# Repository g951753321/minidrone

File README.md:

# Minidrone project

This project is a complex project that involves the firmware development, the schematic, and PCB design for a mini drone.

## Firmware development

The firmware development is done using the Zephyr RTOS. The firmware includes the control algorithms for the drone, and the communication with the MicroBlue application.

### Setup Zephyr RTOS

To setup the Zephyr RTOS, follow the instructions in the [Zephyr RTOS documentation](https://docs.zephyrproject.org/latest/getting_started/index.html).

### Project Initialization

To initial the project, clone the repository and run the following commands:

```bash
west init -m https://github.com/g951753321/minidrone.git --mr main minidrone
cd minidrone
west update
```

### Build the project

To build the project, run the following commands:

```bash
west build -b stm32_dev_min minidrone/apps/PID_control
```

The firmware is built for the `stm32_dev_min` board, and the application is `PID_control`.
The output files are located in the `build/zephyr` directory.

## Schematic and PCB design

The schematic/PCB design is done using KiCad. The schematic includes the design of the motor drivers, the microcontroller, and the sensors.

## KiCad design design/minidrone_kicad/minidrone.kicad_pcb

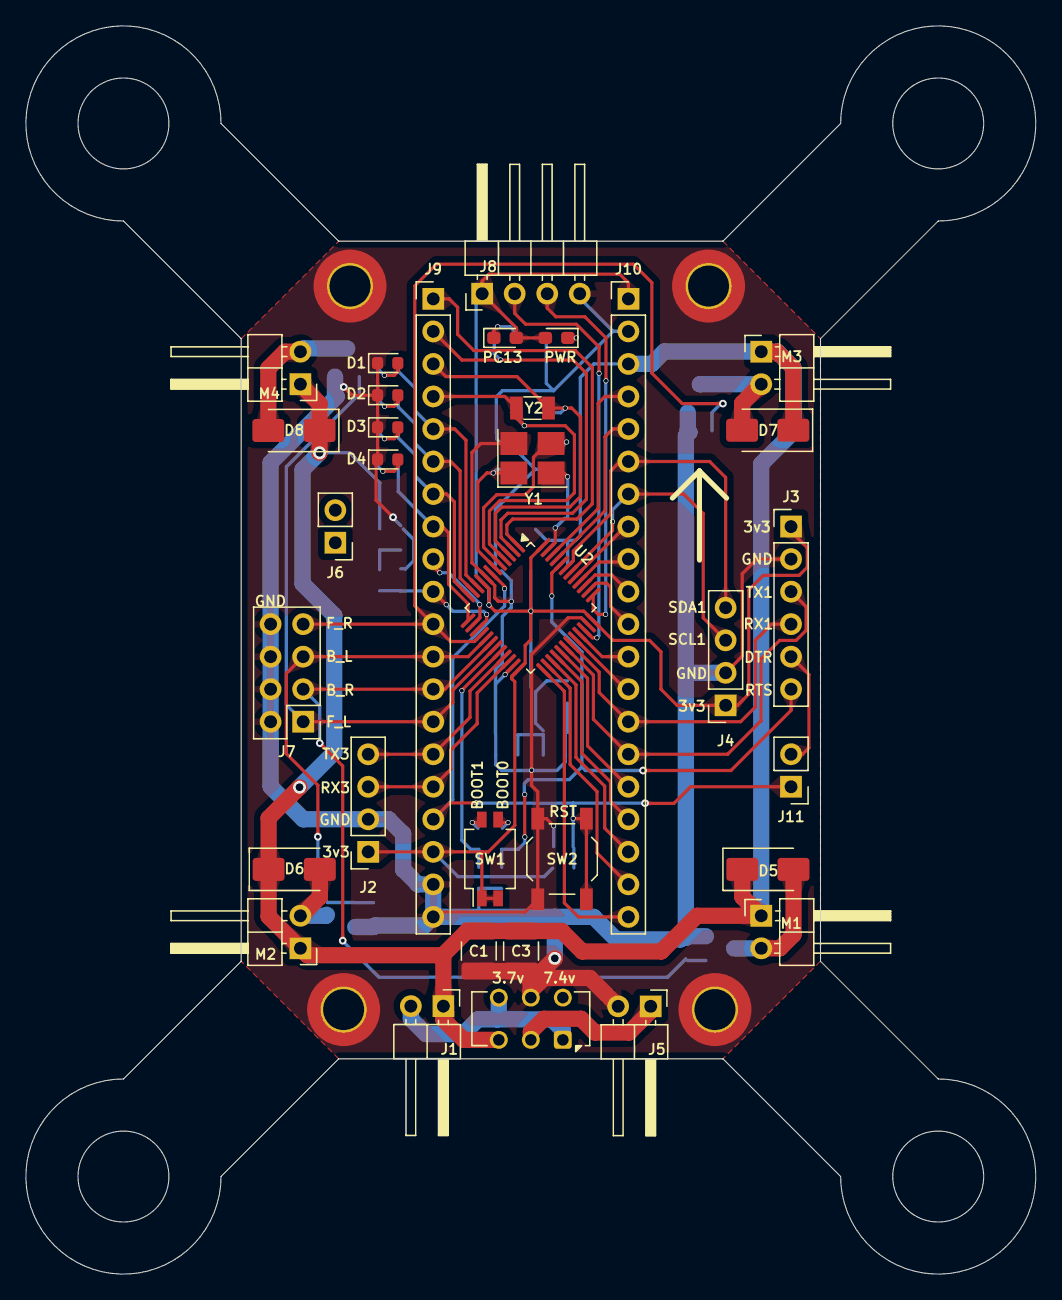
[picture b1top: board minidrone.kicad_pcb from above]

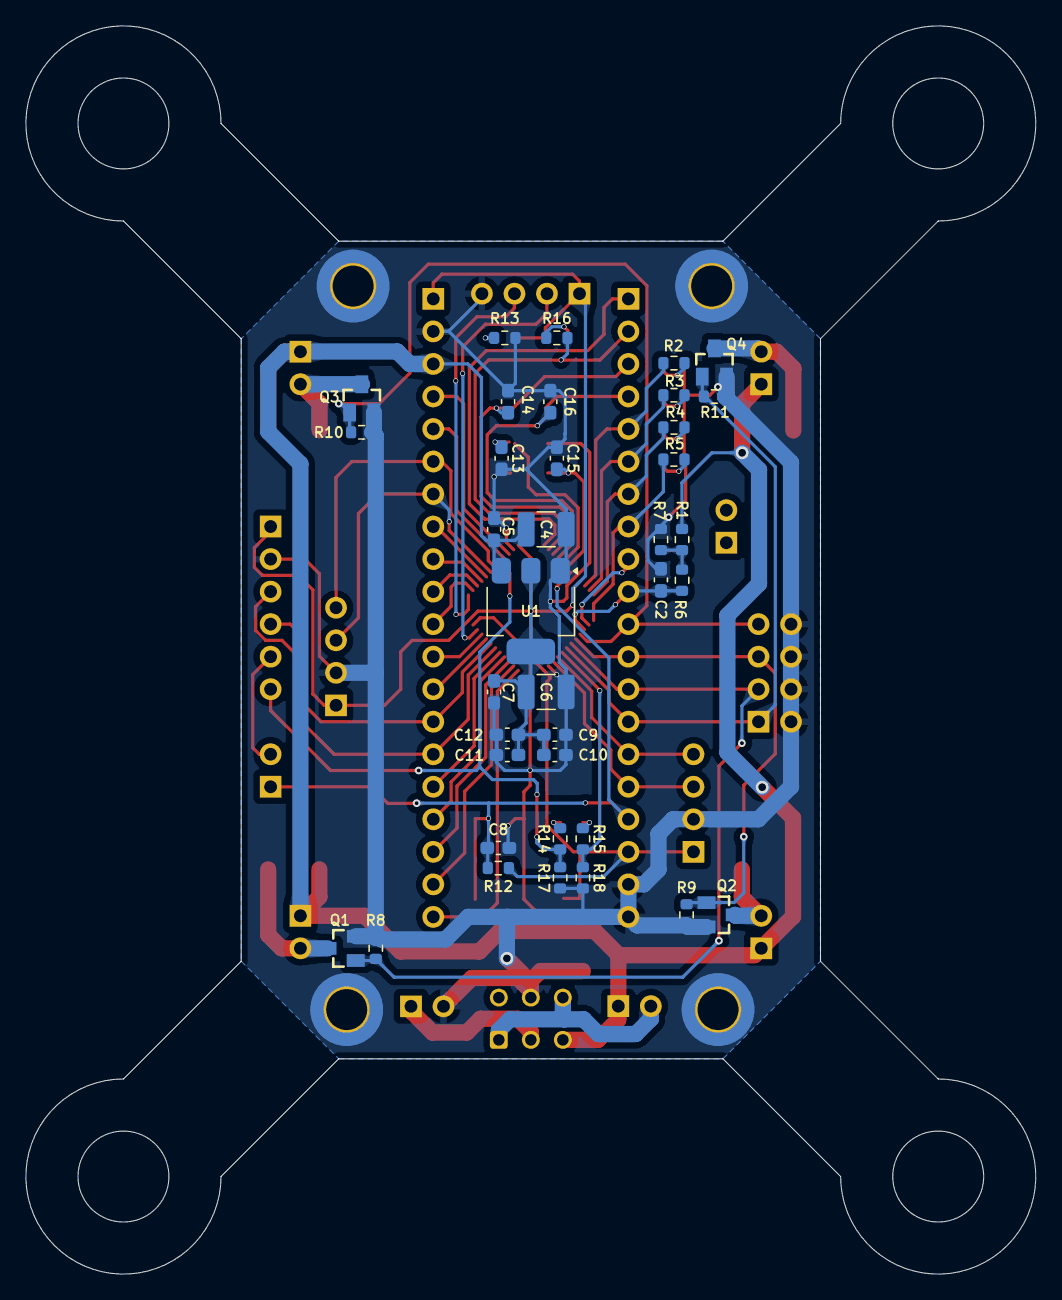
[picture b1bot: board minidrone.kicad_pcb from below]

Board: 2 copper layers, 78.9 x 97.5 mm, 74 parts (37 on the bottom side), 59 nets.

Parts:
C1, C3, C4, C6: 10 uF; C_1210_3225Metric_Pad1.33x2.70mm_HandSolder
C2, C5, C7, C9, C10, C11, C12: 0.1 uF; C_0603_1608Metric_Pad1.08x0.95mm_HandSolder
C8: 1 uF; C_0603_1608Metric_Pad1.08x0.95mm_HandSolder
C13, C15: 20 pF; C_0603_1608Metric_Pad1.08x0.95mm_HandSolder
C14, C16: 12 pF; C_0603_1608Metric_Pad1.08x0.95mm_HandSolder
D1, D2, D3, D4: LED; LED_0603_1608Metric
D5, D6, D7, D8: 1N4007; D_SMA
D9, D10: LED; LED_0603_1608Metric_Pad1.05x0.95mm_HandSolder
H1, H2, H3, H4: Pad; MountingHole_3.2mm_M3_ISO7380_Pad_TopBottom
J1, J5: BAT; PinHeader_1x02_P2.54mm_Horizontal
J2: HM-13 Bluetooth; PinSocket_1x04_P2.54mm_Vertical
J3: programming; PinHeader_1x06_P2.54mm_Vertical
J4: mpu6050; PinSocket_1x04_P2.54mm_Vertical
J6: place_holder; PinHeader_1x02_P2.54mm_Vertical
J7: Conn_02x04_Odd_Even; PinHeader_2x04_P2.54mm_Vertical
J8: J-Link; PinHeader_1x04_P2.54mm_Horizontal
J9, J10: Conn_01x20; PinHeader_1x20_P2.54mm_Vertical
J11: jumper; PinHeader_1x02_P2.54mm_Vertical
M1: BR; PinHeader_1x02_P2.54mm_Horizontal
M2: BL; PinHeader_1x02_P2.54mm_Horizontal
M3: FR; PinHeader_1x02_P2.54mm_Horizontal
M4: FL; PinHeader_1x02_P2.54mm_Horizontal
Q1, Q2, Q3, Q4: SI2302; SOT23
R1, R6: 30 K; R_0603_1608Metric
R2, R3, R4, R5: 180; R_0603_1608Metric
R7, R8, R9, R10, R11, R12, R14, R15: 10 K; R_0603_1608Metric
R13, R16: 1 K; R_0603_1608Metric
R17, R18: 100 K; R_0603_1608Metric
SW1: SW_DIP_x02; SW_DIP_SPSTx02_Slide_Omron_A6H-2101_W6.15mm_P1.27mm
SW2: SW_Push; SW_SPST_TL3342
SW3: V_sw; SW_CK_JS202011CQN_DPDT_Straight
U1: LM1117MP-3.3; SOT-223-3_TabPin2
U2: STM32F103CBTx; LQFP-48_7x7mm_P0.5mm
Y1: 8MHz; Crystal_SMD_3225-4Pin_3.2x2.5mm_HandSoldering
Y2: 32,768KHz; Crystal_SMD_3215-2Pin_3.2x1.5mm

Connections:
+3.3V: C6.1, C7.1, C9.1, C10.1, C11.1, C12.1, D9.2 (A), D10.2 (A), J2.1, J3.1, J4.1, J8.1, J9.18, J10.1, R12.1, SW1.1, SW1.2, U1.2 (VO), U2.9 (VDDA), U2.24 (VDD), U2.36 (VDD), U2.48 (VDD)
+BATT: C1.1, C3.1, C4.1, C5.1, D5.1 (K), D6.1 (K), D7.1 (K), D8.1 (K), J1.1, J10.3, M1.1 (+), M2.1 (+), M3.1 (+), M4.1 (+), R1.1, SW3.3 (C), U1.3 (VI)
/BL_PWM: J7.5, J9.12, Q2.1, R9.1, U2.17 (PA7)
/BR_PWM: J7.3, J9.13, Q1.1, R8.1, U2.18 (PB0)
/BT_RX: J2.4, J9.15, U2.21 (PB10)
/BT_TX: J2.3, J9.16, U2.22 (PB11)
/FL_PWM: J7.1, J9.14, Q4.1, R11.1, U2.19 (PB1)
/FR_PWM: J7.7, J9.11, Q3.1, R10.1, U2.16 (PA6)
/MPU_SCL: J4.3, J10.7, U2.42 (PB6)
/MPU_SDA: J4.4, J10.6, U2.43 (PB7)
/PRG_DTR: J3.5, J11.2
/PRG_RTS: J3.6, R14.1, R17.2, U2.44 (BOOT0)
/PRG_RX: J3.3, J10.15, U2.30 (PA9)
/PRG_TX: J3.4, J10.14, U2.31 (PA10)
/STAT_0: J9.5, R2.1, U2.10 (PA0)
/STAT_1: J9.6, R3.1, U2.11 (PA1)
/STAT_2: J9.7, R4.1, U2.12 (PA2)
/STAT_3: J9.8, R5.1, U2.13 (PA3)
/VBAT_a: C2.1, J9.10, R6.2, U2.15 (PA5)
/stm32_dev/BOOT1: R15.1, R18.2, U2.20 (PB2)
/stm32_dev/OSCIN: C13.2, U2.5 (PD0), Y1.3
/stm32_dev/OSCOUT: C15.1, U2.6 (PD1), Y1.1
/stm32_dev/PA4: J9.9, U2.14 (PA4)
/stm32_dev/PA8: J10.16, U2.29 (PA8)
/stm32_dev/PA11: J10.13, U2.32 (PA11)
/stm32_dev/PA12: J10.12, U2.33 (PA12)
/stm32_dev/PA15: J10.11, U2.38 (PA15)
/stm32_dev/PB3: J10.10, U2.39 (PB3)
/stm32_dev/PB4: J10.9, U2.40 (PB4)
/stm32_dev/PB5: J10.8, U2.41 (PB5)
/stm32_dev/PB8: J10.5, U2.45 (PB8)
/stm32_dev/PB9: J10.4, U2.46 (PB9)
/stm32_dev/PB12: J10.20, U2.25 (PB12)
/stm32_dev/PB13: J10.19, U2.26 (PB13)
/stm32_dev/PB14: J10.18, U2.27 (PB14)
/stm32_dev/PB15: J10.17, U2.28 (PB15)
/stm32_dev/PC13: J9.2, R16.2, U2.2 (PC13)
/stm32_dev/PC14: C14.2, J9.3, U2.3 (PC14), Y2.2
/stm32_dev/PC15: C16.1, J9.4, U2.4 (PC15), Y2.1
/stm32_dev/Reset: C8.1, J9.17, J11.1, R12.2, SW2.2, U2.7 (NRST)
/stm32_dev/SWCLK: J8.3, U2.37 (PA14)
/stm32_dev/SWDIO: J8.2, U2.34 (PA13)
/stm32_dev/VBAT: J9.1, U2.1 (VBAT)
GND: C1.2, C2.2, C3.2, C4.2, C5.2, C6.2, C7.2, C8.2, C9.2, C10.2, C11.2, C12.2, C13.1, C14.1, C15.2, C16.2, D1.1 (K), D2.1 (K), D3.1 (K), D4.1 (K), H1.1, H2.1, H3.1, H4.1, J2.2, J3.2, J4.2, J5.2, J7.2, J7.4, J7.6, J7.8, J8.4, J9.19, J9.20, J10.2, Q1.2, Q2.2, Q3.2, Q4.2, R7.2, R8.2, R9.2, R10.2, R11.2, R13.1, R17.1, R18.1, SW2.1, SW3.5 (B), U1.1 (GND), U2.8 (VSSA), U2.23 (VSS), U2.35 (VSS), U2.47 (VSS), Y1.2, Y1.4
unnamed: D1.2 (A), R2.2
unnamed: D2.2 (A), R3.2
unnamed: D3.2 (A), R4.2
unnamed: D4.2 (A), R5.2
unnamed: D5.2 (A), M1.2 (-), Q1.3
unnamed: D6.2 (A), M2.2 (-), Q2.3
unnamed: D7.2 (A), M3.2 (-), Q3.3
unnamed: D8.2 (A), M4.2 (-), Q4.3
unnamed: D9.1 (K), R13.2
unnamed: D10.1 (K), R16.1
unnamed: J1.2, SW3.1 (A), SW3.4 (A)
unnamed: J5.1, SW3.2 (B)
unnamed: R1.2, R6.1, R7.1
unnamed: R14.2, SW1.3
unnamed: R15.2, SW1.4

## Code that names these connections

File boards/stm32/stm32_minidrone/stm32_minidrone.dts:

/*
 * SPDX-License-Identifier: Apache-2.0
 *
 * STM32 MiniDrone Board Device Tree
 *
 * Pin mapping (from KiCad schematic):
 *   PA0-PA3  : STAT_0..STAT_3 (GPIO LEDs)
 *   PA5      : VBAT_a (ADC1_IN5, battery voltage)
 *   PA6      : FR_PWM (TIM3_CH1)
 *   PA7      : BL_PWM (TIM3_CH2)
 *   PA9/PA10 : USART1 (debug console)
 *   PB0      : BR_PWM (TIM3_CH3)
 *   PB1      : FL_PWM (TIM3_CH4)
 *   PB6/PB7  : I2C1 (MPU6050)
 *   PB10/PB11: USART3 (HM-13 Bluetooth)
 *   PC13     : PWR LED
 */

/dts-v1/;
#include <st/f1/stm32f103Xb.dtsi>
#include <st/f1/stm32f103r(8-b)tx-pinctrl.dtsi>

/ {
	model = "STM32 minidrone Board";
	compatible = "st,stm32f103cb";

	chosen {
		zephyr,console = &usart1;
		zephyr,shell-uart = &usart1;
		zephyr,sram = &sram0;
		zephyr,flash = &flash0;
	};

	leds {
		compatible = "gpio-leds";

		pwr_led: pwr_led {
			gpios = <&gpioc 13 GPIO_ACTIVE_LOW>;
			label = "PWR";
		};

		stat0: stat_0 {
			gpios = <&gpioa 0 GPIO_ACTIVE_HIGH>;
			label = "STAT_0";
		};

		stat1: stat_1 {
			gpios = <&gpioa 1 GPIO_ACTIVE_HIGH>;
			label = "STAT_1";
		};

		stat2: stat_2 {
			gpios = <&gpioa 2 GPIO_ACTIVE_HIGH>;
			label = "STAT_2";
		};

		stat3: stat_3 {
			gpios = <&gpioa 3 GPIO_ACTIVE_HIGH>;
			label = "STAT_3";
		};
	};

	aliases {
		led0 = &pwr_led;
		stat0 = &stat0;
		stat1 = &stat1;
		stat2 = &stat2;
		stat3 = &stat3;
		bt-uart = &usart3;
	};
};

&clk_hse {
	clock-frequency = <DT_FREQ_M(8)>;
	status = "okay";
};

&pll {
	mul = <9>;
	clocks = <&clk_hse>;
	status = "okay";
};

&rcc {
	clocks = <&pll>;
	clock-frequency = <DT_FREQ_M(72)>;
	ahb-prescaler = <1>;
	apb1-prescaler = <2>;
	apb2-prescaler = <1>;
};

/* Debug console */
&usart1 {
	pinctrl-0 = <&usart1_tx_pa9 &usart1_rx_pa10>;
	pinctrl-names = "default";
	current-speed = <115200>;
	status = "okay";
};

/* Bluetooth HM-13 */
&usart3 {
	pinctrl-0 = <&usart3_tx_pb10 &usart3_rx_pb11>;
	pinctrl-names = "default";
	current-speed = <38400>;
	status = "okay";
};

/* IMU MPU6050 */
&i2c1 {
	pinctrl-0 = <&i2c1_scl_pb6 &i2c1_sda_pb7>;
	pinctrl-names = "default";
	status = "okay";
	clock-frequency = <I2C_BITRATE_FAST>;

	mpu6050: mpu6050@68 {
		compatible = "invensense,mpu6050";
		reg = <0x68>;
		status = "okay";
		int-gpios = <&gpiob 5 GPIO_ACTIVE_HIGH>;
	};
};

/* Motor PWM: TIM3 CH1-CH4 on PA6, PA7, PB0, PB1 */
&timers3 {
	st,prescaler = <0>;
	status = "okay";

	motor_pwm: pwm {
		compatible = "st,stm32-pwm";
		status = "okay";
		pinctrl-0 = <&tim3_ch1_pwm_out_pa6
			     &tim3_ch2_pwm_out_pa7
			     &tim3_ch3_pwm_out_pb0
			     &tim3_ch4_pwm_out_pb1>;
		pinctrl-names = "default";
		#pwm-cells = <3>;
	};
};

/* Battery voltage ADC on PA5 (ADC1_IN5) */
&adc1 {
	pinctrl-0 = <&adc1_in5_pa5>;
	pinctrl-names = "default";
	status = "okay";
	#address-cells = <1>;
	#size-cells = <0>;

	channel@5 {
		reg = <5>;
		zephyr,gain = "ADC_GAIN_1";
		zephyr,reference = "ADC_REF_INTERNAL";
		zephyr,acquisition-time = <ADC_ACQ_TIME_DEFAULT>;
		zephyr,resolution = <12>;
	};
};

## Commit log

2024-07-25 feat(drivers): Create custom joystick driver
    Create custom joystick with compatible the MicroBlue application.
2024-07-26 refactor(DTS): Rename the PWM nodes
2024-07-28 docs(SCH/PCB): Add electrical schematic and PCB layout
2024-07-28 docs(README): Add the README file
2024-08-10 fix(PCH/PCB): Programming pins and motor pins definition.
    Correct the programming TX/RX connection.
    Update the motor net-names due to the design changed.
2024-08-10 test(hardware): Light the LEDs with PWM controller.
2024-08-22 docs(SCH/PCB): Update the PCB design to v2.
    The v1's handmade version is too heavy.
    - Remove the STM32 blue pill board.
    - Using the STM32F103CBT6 to make sure the ROM size enough.
    - Design the PCB as the drone's frame.
2024-09-29 fix(SCH/PCB): The reset button no function
2026-01-01 fix(circuit): fix the battery series or parallel circuits
    - Correct the invert connection on SW3
    - Correct the silkscreen for voltage selection
2026-01-01 fix(circuit): add mounting hole
2026-03-24 chore: add stm32_minidrone board
    - add stm32_minidrone board
    - remove test code
2026-03-24 docs(design): add VSDD Phase 1 specification suite
    Replace informal BOM.md and feature.md with comprehensive spec documents
    following the Verified Spec-Driven Development (VSDD) methodology.
    Specs cover hardware, features, protocols (MicroBlue BT), mechanical,
    safety, performance, behavioral contracts, and verification architecture.
    Includes adversarial review fixes for motor mixer, voltage divider,
    PWM resolution, PID controller count, and failsafe consistency.
2026-03-24 fix(board): add full_name to board.yml and driver stubs
    board.yml requires full_name alongside name per Zephyr board schema.
    Add empty Kconfig and CMakeLists.txt in drivers/ to unblock builds.
2026-03-24 feat(core): add pure core module headers
    Define interfaces for all pure core modules per VSDD spec:
    - state_machine.h: 3-mode FSM with event processing
    - pid.h: PID controller with anti-windup
    - mixer.h: X-quad motor mixing with clamping
    - input_mapper.h: joystick and slider-to-gain mapping
    - battery.h: ADC conversion and hysteresis level detection
2026-03-24 feat(core): implement pure core modules
    Minimal TDD implementations for all pure core modules:
    - state_machine: 3-mode FSM with debounce, cutoff, and tilt handling
    - pid: P/I/D with integrator windup clamp at +/-500
    - mixer: X-quad motor mixing, output clamped to [0, MAX_THROTTLE]
    - input_mapper: joystick center=512→0, slider-to-gain with clamping
    - battery: ADC-to-mV conversion (30K/20K divider), hysteresis levels
2026-03-24 test(core): add Ztest suite and abstract input interface
    VSDD Phase 2: 55 tests across 7 suites (state_machine, pid, mixer,
    input_mapper, battery, parser, calibration) all passing on native_sim.
    Update specs to decouple input from MicroBlue:
    - Add abstract drone_cmd_t interface in behavioral.md
    - Add input/telemetry backend interfaces
    - Update verification purity boundary map
2026-03-24 fix(core): address adversarial review findings
    VSDD Phase 3/4 fixes from adversarial code roast:
    - state_machine: carry calibration_valid/last_disarm_ms in sm_result_t;
    add sm_apply() helper; cutoff in Calibrate transitions to Diag;
    add REPORT_LOWBATT on critical; invalid mode returns MOTORS_OFF
    - calibration: use int64_t for sum/variance to prevent overflow
    - pid: guard derivative term with dt > 1e-6f to prevent Inf/NaN
2026-03-24 test(core): harden tests from adversarial review
    - Fix tautological PID zero-error test; add sign convention test
    - Add near-zero dt safety test for PID derivative
    - Assert exact ADC conversion value (8250 mV) instead of fuzzy range
    - Mixer negative test asserts specific expected duty values
    - Parser oversized ID test asserts unconditional rejection
    - Add joystick out-of-range clamp test
2026-03-24 fix(parser): reject non-printable ASCII in ID and VALUE fields
    Fuzz testing (libFuzzer, 1M iterations) found that null bytes in ID or
    VALUE fields caused strlen() to return 0 on seemingly valid messages,
    violating VP-15 (valid output has non-empty id and value).
    Validate that all ID and VALUE bytes are printable ASCII (0x20-0x7E)
    before accepting the message.
2026-03-24 test(verify): add CBMC proof harnesses and libFuzzer harness
    VSDD Phase 5 formal hardening artifacts:
    - tests/fuzz/fuzz_parser.c: libFuzzer harness for VP-14..VP-17
    - tests/cbmc/proof_pid.c: VP-06 (windup), VP-08 (no overflow)
    - tests/cbmc/proof_mixer.c: VP-07/VP-21 (clamped), VP-22 (no negative)
    - tests/cbmc/proof_battery.c: VP-10 (no overflow), VP-18 (hysteresis)
    - tests/cbmc/proof_input_mapper.c: VP-09 (center=0), VP-23 (gain bounds)
2026-03-29 chore: pin Zephyr to v4.1.0 release
    Use a stable tagged release instead of tracking main to ensure
    reproducible builds.
2026-03-29 fix(board): rewrite DTS and defconfig to match KiCad schematic
    Align the device tree with the actual Rev 1 PCB pin mapping:
    - Add PA0-PA3 status LEDs, PC13 power LED with proper aliases
    - Route ADC to PA5 (ADC1_IN5) for battery sensing
    - Route TIM3 CH1-CH4 to PA6/PA7/PB0/PB1 for motor PWM
    - Add MPU6050 I2C child node on I2C1 (PB6/PB7)
    - Set USART3 (PB10/PB11) to 38400 baud for HM-13 Bluetooth
2026-03-29 fix(core): correct battery voltage divider and calibration threshold
    - Update voltage divider ratio from 0.4 (30K/20K) to 0.25 (30K/10K)
    to match actual circuit: formula becomes adc_raw * 13200 / 4095
    - Raise calibration variance threshold from 100 to 10000 to accommodate
    real IMU noise during power-on with shared 3.3V rail (see HW-08)
    - Update CBMC proof assertion bound to 14000 mV for new formula
2026-03-29 feat(core): add effectful shell module interfaces
    Add shell.h defining the hardware abstraction layer between the pure
    core logic and Zephyr drivers (BT, IMU, motor, battery, LED).
    Each module is Kconfig-gated; disabled modules compile as no-op stubs.
2026-03-29 feat(app): add flight controller application with shell modules
    Add the main Zephyr application implementing the full flight controller
    data flow: BT command polling, IMU calibration, PID control loop at
    500 Hz, motor mixing, battery monitoring with hysteresis, and telemetry.
    Shell modules:
    - shell_bt: HM-13 UART RX (ISR ring buffer) + TX, MicroBlue protocol
    - shell_imu: MPU6050 via Zephyr sensor API
2026-03-29 docs(design): add hardware issues tracker for Rev 1 PCB
    Document 13 known hardware issues found during board bring-up:
    - BLOCKING: missing MOSFET gate pull-down resistors (HW-01)
    - Circuit: reverse polarity, overcurrent, LC filter, gate resistors, ESD
    - Power: IMU/BT power sequence, inefficient LDO
    - EMI: BT/IMU placement interference
    - Mechanical: weight budget (74g, target <50g), power switch, BOOT0
2026-04-10 refactor(design): reorganize gen1 files into design/gen1/
    Move spec, kicad, and 3d_models under design/gen1/ to
    prepare for gen2 design alongside gen1 in the same repo.
    Rename minidrone_kicad to kicad.
2026-04-10 docs(design): add gen2 drone specification
    Modular architecture: STM32H743VIH6 core module (40x25mm)
    with castellated pads, drone-specific carrier board (50x50mm).
    - 2S/3S LiPo with per-cell monitoring via JST-XH balance port
    - ICM-42688-P IMU, BMP390 baro, VL53L5CX ToF, PMW3901 OF
    - ELRS 2.4GHz primary control, BLE 5.0 config/OTA
    - Bidirectional DSHOT300 with BlueJay ESC for RPM telemetry
2026-04-11 docs(design): update gen2 to 3S/1404 with GPS and camera
    Finalize gen2 spec on single 3S configuration with 1404
    4500KV motors, CNHL 850mAh battery, and removable module
    connectors.
    - Replace 1204 motors with 1404 4500KV (800g total thrust)
    - Remove 2S config; 3S only (CNHL MiniStar 850mAh 70C)
    - AUW 141g, T/W 5.7:1, hover time ~26 min
2026-04-11 fix(design): remove stale charger references from gen2
    USB-C function listed "battery charging" and safety ESD
    table referenced "Charger IC handles OVP", but there is
    no onboard charger — external balance charger only.
2026-04-11 docs(design): add auto-land, MCUboot, BLE shell, MicroSD
    - Sensor load switch (TPS22918) for controlled power
    sequence; fixes Gen 1 HW-08
    - Auto-land on ELRS failsafe when altitude >= 2m
    (descend 0.5 m/s with position hold)
    - MCUboot dual-bank swap with automatic rollback on
    failed OTA update
